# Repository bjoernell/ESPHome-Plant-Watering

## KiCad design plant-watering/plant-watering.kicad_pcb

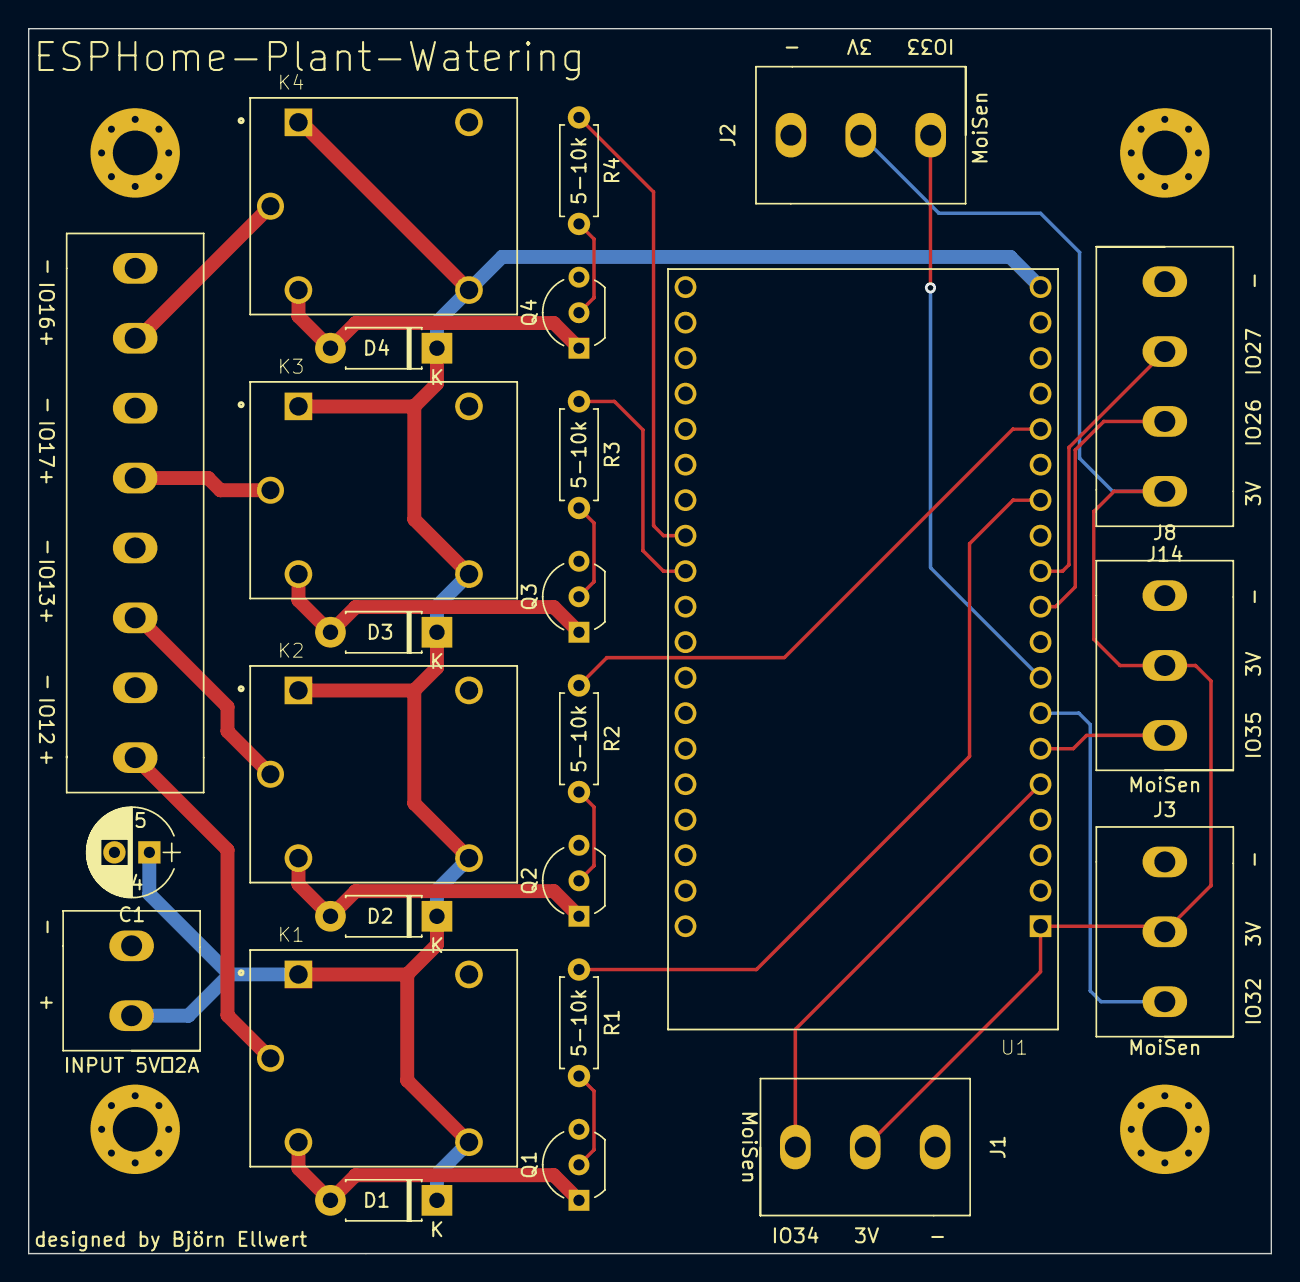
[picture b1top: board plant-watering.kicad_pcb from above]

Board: 2 copper layers, 88.9 x 87.6 mm, 25 parts (0 on the bottom side), 25 nets.

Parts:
C1: 100uF; CP_Radial_D6.3mm_P2.50mm
D1, D2, D3, D4: D; D_DO-41_SOD81_P7.62mm_Horizontal
J1, J2, J3, J8: Conn_01x03_Male; ScrewTerminal_1x3_P5.00
J4: Input; ScrewTerminal_1x2_P5.00
J5: Screw_Terminal_01x08; ScrewTerminal_1x8_P5.00
J14: Conn_01x04_Female; ScrewTerminal_1x4_P5.00
K1, K2, K3, K4: SRD-05VDC-SL-C; RELAY_SRD-05VDC-SL-C
Q1, Q2, Q3, Q4: BC337; TO-92_Inline_Wide
R1, R2, R3, R4: 5k; R_Axial_DIN0207_L6.3mm_D2.5mm_P7.62mm_Horizontal
U1: ESP32-DEVKITC-32D; MODULE_ESP32-DEVKITC-32D

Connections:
+3V3: J1.2, J2.2, J3.2, J8.2, J14.1, U1.1
+5V: C1.1, D1.1, D2.1, D3.1, D4.1, J4.2, K1.A1, K1.NO, K2.A1, K2.NO, K3.A1, K3.NO, K4.A1, K4.NO, U1.19
GND: C1.2, J1.1, J2.1, J3.1, J4.1, J5.2, J5.4, J5.6, J5.8, J8.1, J14.4, Q1.3, Q2.3, Q3.3, Q4.3, U1.14, U1.20, U1.26
GPIO12: R1.1, U1.13
GPIO13: R2.1, U1.15
GPIO16: R4.1, U1.31
GPIO17: R3.1, U1.30
GPIO26: J14.2, U1.10
GPIO27: J14.3, U1.11
GPIO32: J3.3, U1.7
GPIO33: J2.3, U1.8
GPIO34: J1.3, U1.5
GPIO35: J8.3, U1.6
M1: J5.1, K1.COM
M2: J5.3, K2.COM
M3: J5.5, K3.COM
M4: J5.7, K4.COM
unnamed: Q1.2, R1.2
unnamed: Q2.2, R2.2
unnamed: Q3.2, R3.2
unnamed: Q4.2, R4.2
RelayS1: D1.2, K1.A2, Q1.1
RelayS2: D2.2, K2.A2, Q2.1
RelayS3: D3.2, K3.A2, Q3.1
RelayS4: D4.2, K4.A2, Q4.1

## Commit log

2021-01-20 schematic edited
2021-01-21 added many schematicy
2021-01-22 changed transistor and relay circuit
2021-01-22 edited schematic & started pcb design
2021-01-24 started pcb design
2021-01-24 added several parts#
2021-01-25 changed pcb parts
2021-01-25 changed parts on pcb
2021-01-25 finished pcb for now
2021-01-25 added missing route
2021-01-26 added missing text
2021-01-26 generated gerber files and step file
2021-01-27 changed smth. finished and ordered
2021-01-27 forgot to save
